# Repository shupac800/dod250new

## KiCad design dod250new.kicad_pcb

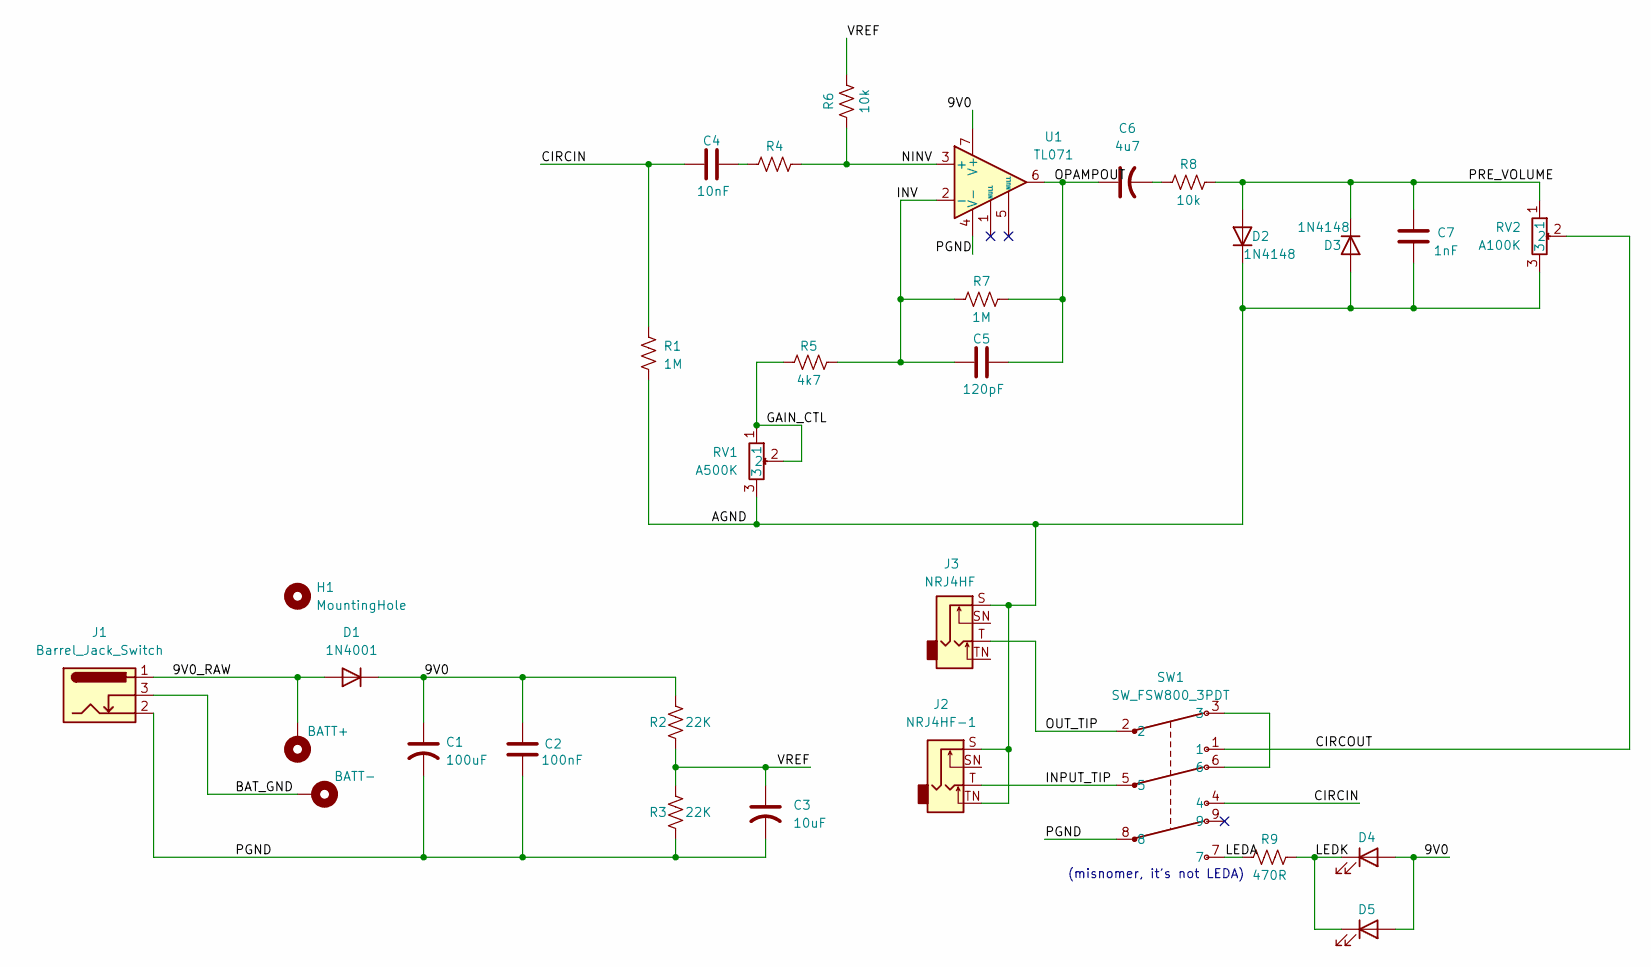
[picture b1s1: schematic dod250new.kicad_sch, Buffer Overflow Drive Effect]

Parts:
C1: 100uF; CP_Radial_D6.3mm_P2.50mm
C2: 100nF; C_Rect_L7.2mm_W4.5mm_P5.00mm
C3: 10uF; C_Radial_D5.0mm_H7.0mm_P2.00mm
C4: 10nF; C_Rect_L7.2mm_W4.5mm_P5.00mm
C5: 120pF; C_Disc_D3.8mm_W2.6mm_P2.50mm
C6: 4u7; CP_Radial_D5.0mm_P2.50mm
C7: 1nF; C_Rect_L7.2mm_W4.5mm_P5.00mm
D1: 1N4001; D_DO-41_SOD81_P10.16mm_Horizontal
D2, D3: 1N4148; D_DO-35_SOD27_P7.62mm_Horizontal
D4, D5: LED; LED_D3.0mm
H1: MountingHole; MountingHole_5.3mm_M5
H2: BATT+; MountingHole_2.2mm_M2_DIN965_Pad
H3: BATT-; MountingHole_2.2mm_M2_DIN965_Pad
J1: Barrel_Jack_Switch; BarrelJack_GCT_DCJ200-10-A_Horizontal
J2: NRJ4HF-1; Jack_6.35mm_Neutrik_NRJ4HF_Horizontal
J3: NRJ4HF; Jack_6.35mm_Neutrik_NRJ4HF_Horizontal
R1, R7: 1M; R_Axial_DIN0207_L6.3mm_D2.5mm_P7.62mm_Horizontal
R2, R3: 22K; R_Axial_DIN0207_L6.3mm_D2.5mm_P7.62mm_Horizontal
R4, R6, R8: 10k; R_Axial_DIN0207_L6.3mm_D2.5mm_P7.62mm_Horizontal
R5: 4k7; R_Axial_DIN0207_L6.3mm_D2.5mm_P7.62mm_Horizontal
R9: 470R; R_Axial_DIN0207_L6.3mm_D2.5mm_P7.62mm_Horizontal
RV1: A500K; POT_ALPHA_RV16_VERT
RV2: A100K; POT_ALPHA_RV16_VERT
SW1: SW_FSW800_3PDT
U1: TL071; DIP-8_W7.62mm

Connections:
/9V0: C1.1, C2.1, D1.1 (K), D4.2 (A), D5.2 (A), R2.2, U1.7 (V+)
/9V0_RAW: D1.2 (A), H2.1 (1_1), J1.1
/AGND: C7.2, D2.1 (K), D3.2 (A), J2.S, J2.TN, J3.S, R1.1, RV1.3, RV2.3
/BAT_GND: H3.1 (1_1), J1.3
/CIRCIN: C4.2, R1.2, SW1.4
/CIRCOUT: RV2.2, SW1.1
/GAIN_CTL: R5.1, RV1.1, RV1.2
/INPUT_TIP: J2.T, SW1.5
/INV: C5.2, R5.2, R7.2, U1.2 (-)
/LEDA: R9.2, SW1.7
/LEDK: D4.1 (K), D5.1 (K), R9.1
/NINV: R4.2, R6.1, U1.3 (+)
/OPAMPOUT: C5.1, C6.1, R7.1, U1.6
/OUT_TIP: J3.T, SW1.2
/PGND: C1.2, C2.2, C3.2, J1.2, R3.1, SW1.8, U1.4 (V-)
/PRE_VOLUME: C7.1, D2.2 (A), D3.1 (K), R8.1, RV2.1
/VREF: C3.1, R2.1, R3.2, R6.2
unnamed: C4.1, R4.1
unnamed: C6.2, R8.2
unnamed: SW1.3, SW1.6

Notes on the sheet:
(misnomer, it's not LEDA)

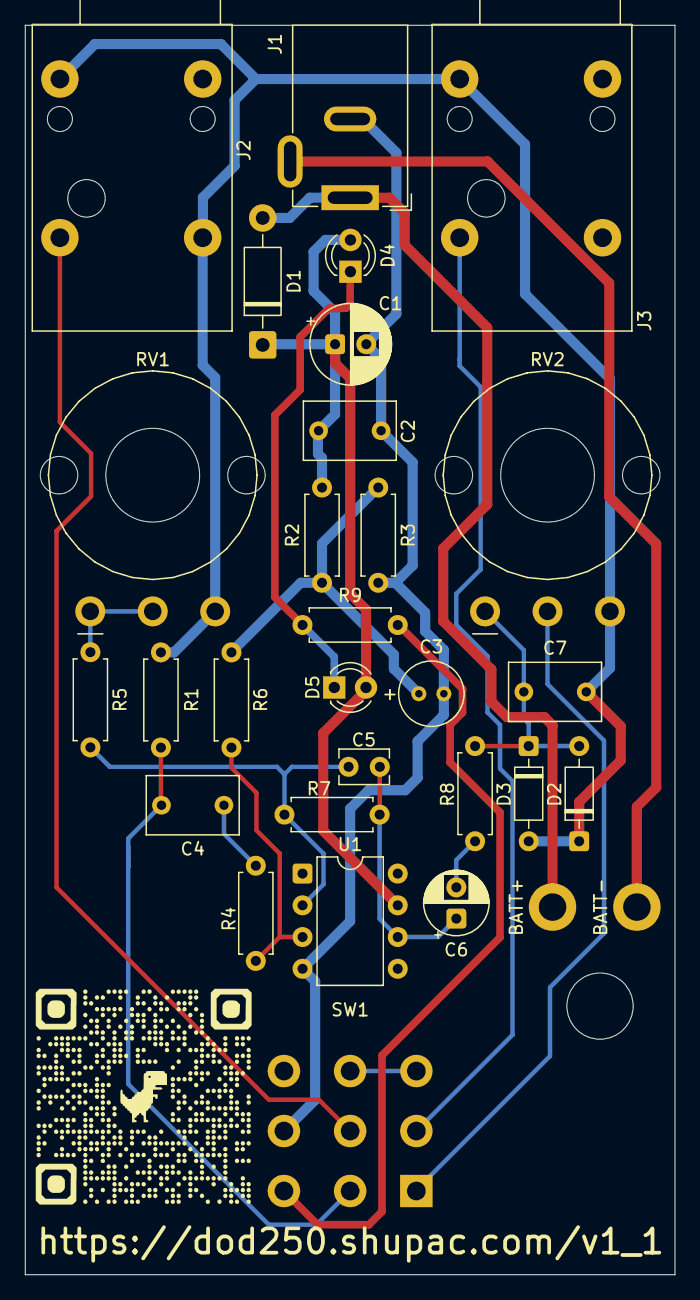
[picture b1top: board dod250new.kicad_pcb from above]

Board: 2 copper layers, 52.0 x 100.0 mm, 31 parts (0 on the bottom side), 20 nets.

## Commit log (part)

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2026-06-04 version sent to JLCPCB 6/4/26
2026-06-05 v1.1 sent to JLCPC 6/4/26 evening -- resolved 9V0 battery net disconnect
2026-06-08 minor tweaks
